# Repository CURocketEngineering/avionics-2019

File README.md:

## Deprecated
For more information, visit the [new, Python implementation](https://github.com/CURocketEngineering/avionics_main).

### About
Clemson University Rocket Engineering (CURE) Avionics subteam program files. 
Powers CURE's competitive and non-competitive rockets. Used in the 
Intercollegiate Rocket Engineering Competition. Begun by Foster McLane, 2016.

### Documentation
* [`base/`](base/)
  * Code ran on the CURE base station for communication and telemetry
  * `main.py` for basic communication
  * `mpl.py` for graphical interpretation
  * `mpl_simulator.py` for simulating graphical interpretation
* [`cad/`](/cad)
  * Files for electrically engineering components in `eagle`
* [`data/`](data/)
  * Flight data
  * `jsongrapher.py` for ensuring simulation (and actual) data 
  * ['Complete simulation'](data/sim_data_graphed) for pictures of complete simulations
* [`extra/`](extra/)
  * Testing
  * GPS and XBEE `.ino` files
* [`main/`](main/)
  * Code ran on CURE rockets used for data collection, state changes, and telemetry
* [`pics/`](pics/)
  * Pictures used in this github
* [`xbee/bypass/`](xbee/bypass/)
  * Communication

### License
This project is licensed used the GNU General Public License v3.0

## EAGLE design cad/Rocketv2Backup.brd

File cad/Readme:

Sparkfun Names of sensors (in eagle "add" component):
   1. Venus GPS ->                   GPS/ VENUS638FLPX-L
   2. Atmospheric Sensor Breakout -> Sensors/ BME280
   3. 9DoF Sensor Stick ->           Sensors/ LSM9DS1
   4. Antenna ->                     RF/ XBEE

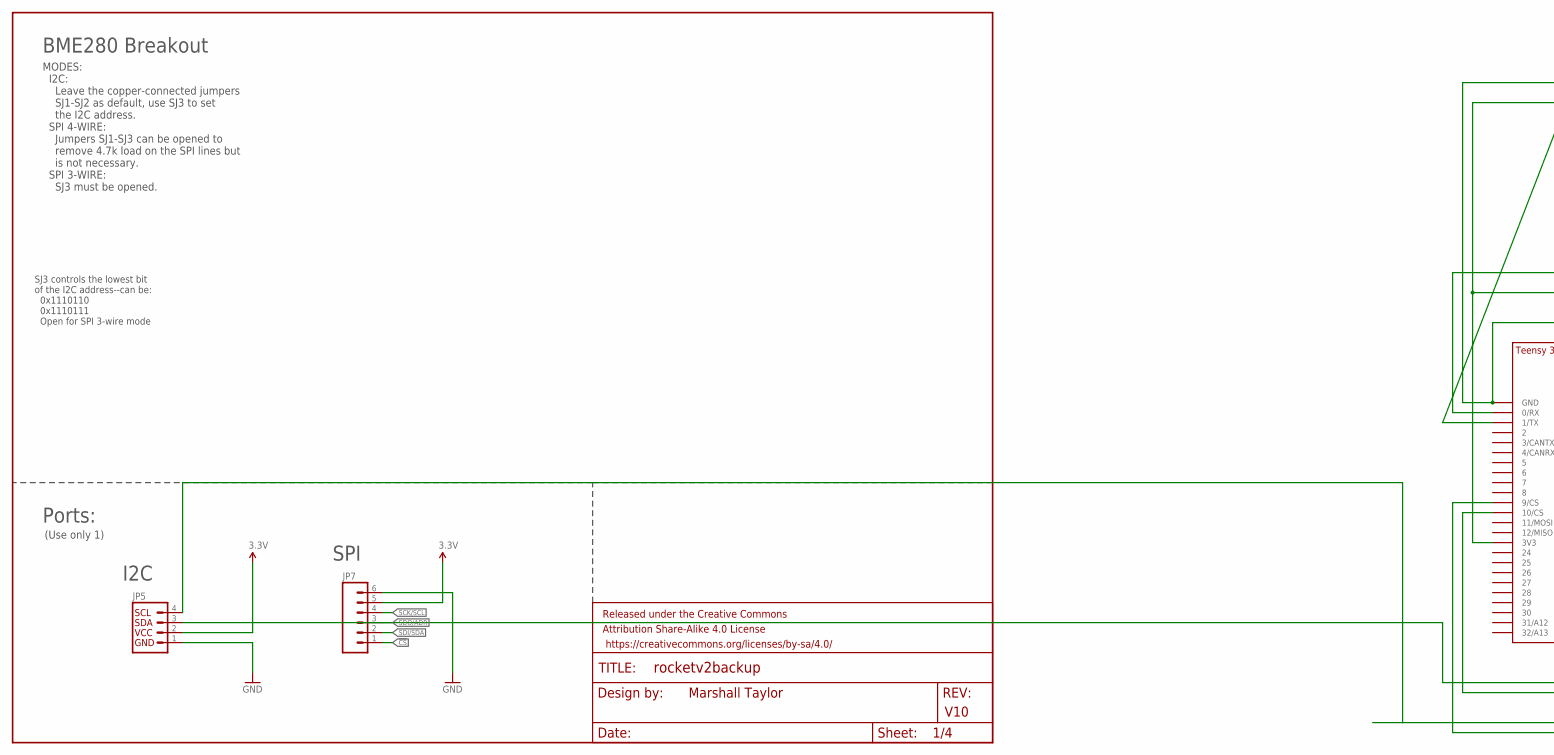
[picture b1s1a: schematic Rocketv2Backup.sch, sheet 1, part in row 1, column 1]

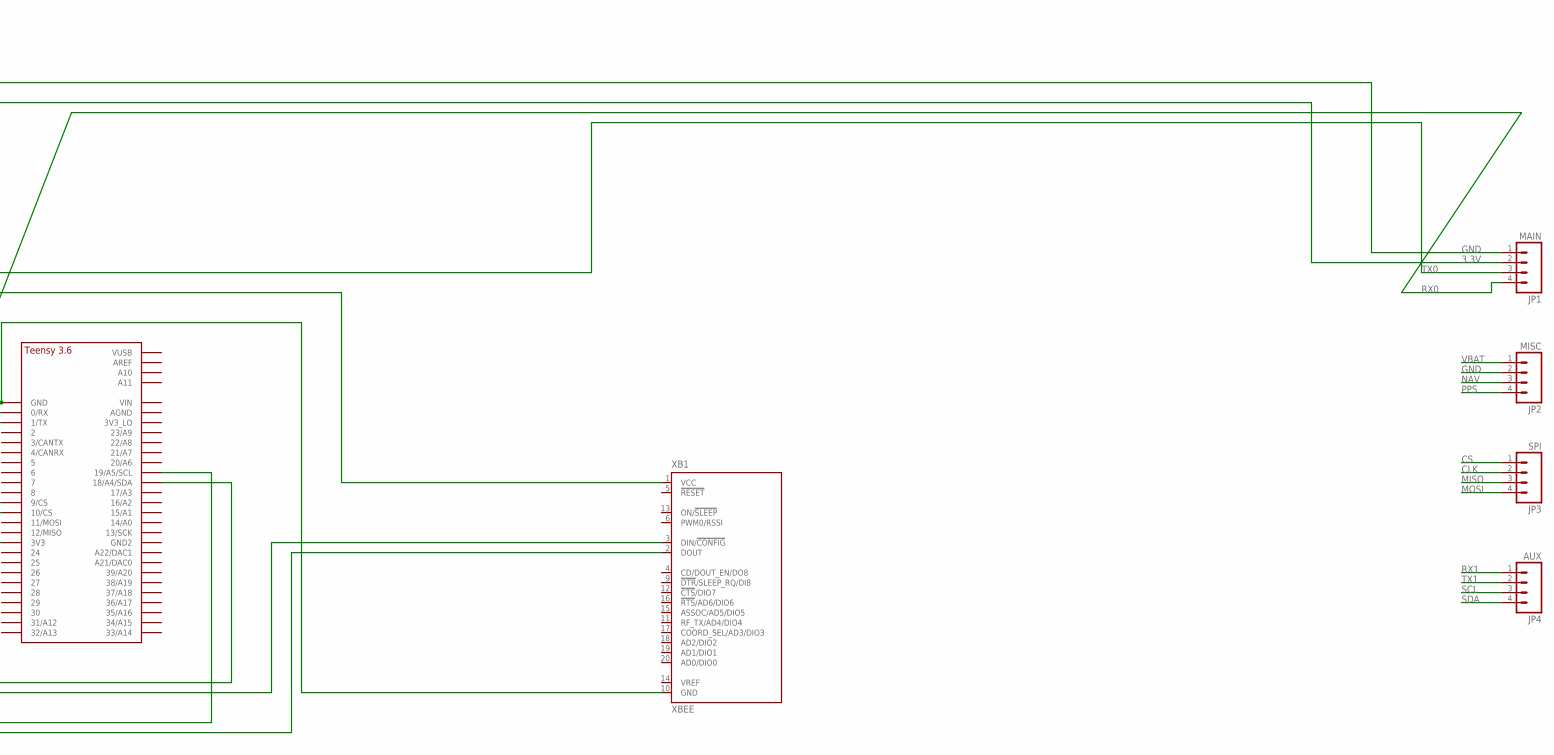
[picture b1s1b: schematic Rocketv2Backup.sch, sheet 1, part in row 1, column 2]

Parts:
FRAME3: FRAME-LETTER; CREATIVE_COMMONS
JP1: MAIN; 1X04
JP2: MISC; 1X04
JP3: SPI; 1X04
JP4: AUX; 1X04
JP5: I2C_STANDARD_NO_SILK; 1X04_NO_SILK
JP7: M06NO_SILK_FEMALE_PTH; 1X06_NO_SILK
U$1: TEENSY_3.5/3.6_BASIC
XB1: XBEE

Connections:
3.3V: JP1.2, JP5.2, JP7.5, U$1.3V3, XB1.1 (VCC)
!CS: JP7.1
CLK: JP3.2
CS: JP3.1
GND: JP1.1, JP2.2, JP5.1, JP7.6, U$1.GND, XB1.10 (GND); also elsewhere on the board
MISO: JP3.3
MOSI: JP3.4
unnamed: JP5.4, U$1.19/A5/SCL
unnamed: U$1.10/CS, XB1.3 (DIN/!CONFIG)
unnamed: U$1.9/CS, XB1.2 (DOUT)
NAV: JP2.3
PPS: JP2.4
RX0: JP1.4, U$1.1/TX
RX1: JP4.1
SCK/SCL: JP7.4
SCL: JP4.3; also elsewhere on the board
SDA: JP4.4; also elsewhere on the board
SDI/SDA: JP5.3, JP7.2, U$1.18/A4/SDA
SDO/ADR: JP7.3
TX0: JP1.3, U$1.0/RX
TX1: JP4.2
VBAT: JP2.1

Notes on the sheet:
Marshall Taylor
V10
BME280 Breakout
SJ3 controls the lowest bit of the I2C address--can be: 0x1110110 0x1110111 Open for SPI 3-wire mode
Ports:
(Use only 1)
I2C
SPI
MODES: I2C: Leave the copper-connected jumpers SJ1-SJ2 as default, use SJ3 to set the I2C address. SPI 4-WIRE: Jumpers SJ1-SJ3 can be opened to remove 4.7k load on the SPI lines but is not necessary. SPI 3-WIRE: SJ3 must be opened.

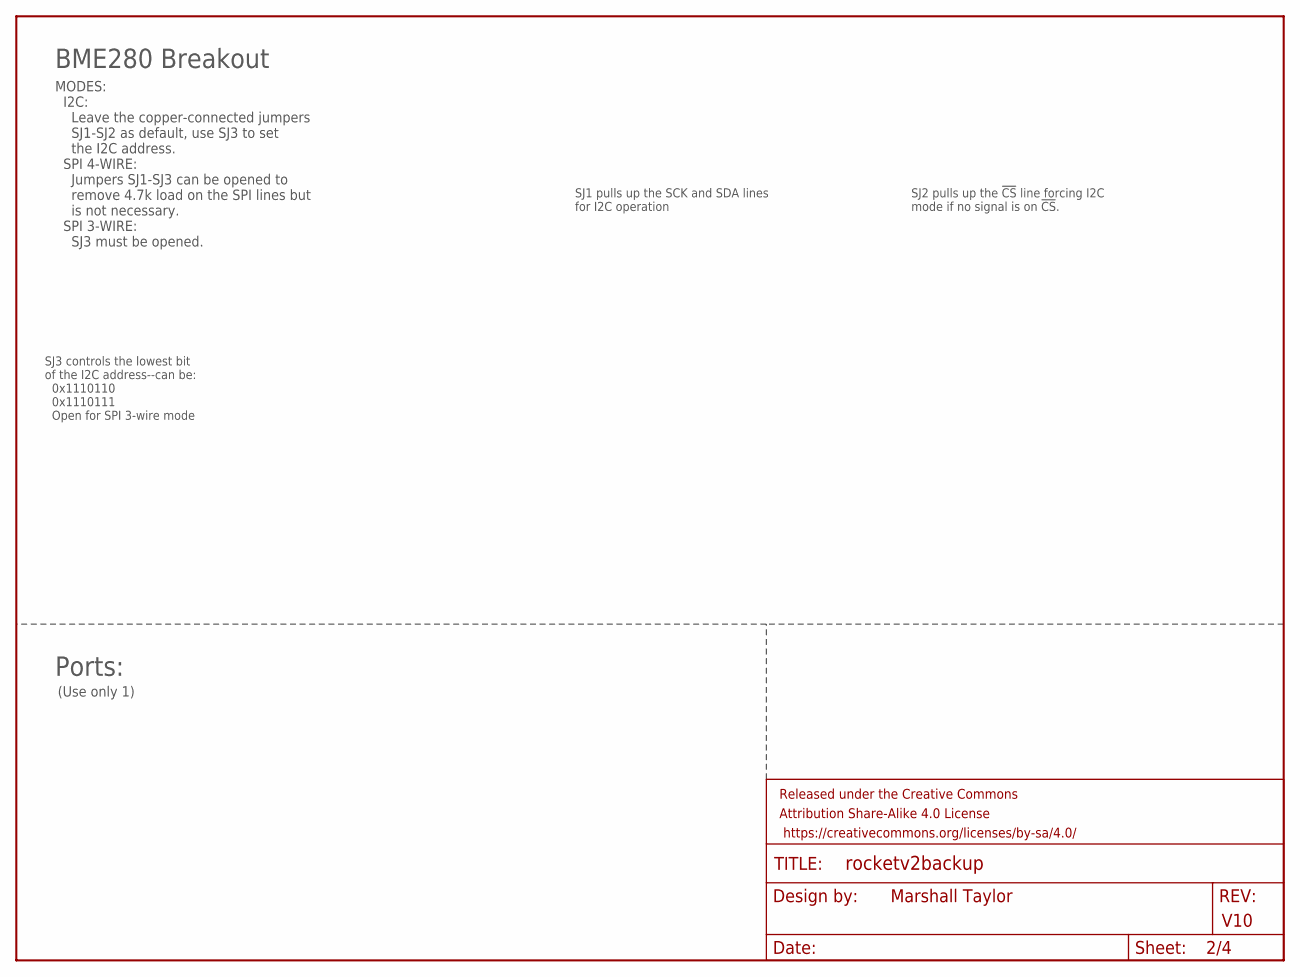
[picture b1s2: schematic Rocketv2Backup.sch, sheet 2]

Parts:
FRAME1: FRAME-LETTER; CREATIVE_COMMONS

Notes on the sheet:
Marshall Taylor
V10
BME280 Breakout
SJ3 controls the lowest bit of the I2C address--can be: 0x1110110 0x1110111 Open for SPI 3-wire mode
SJ1 pulls up the SCK and SDA lines for I2C operation
Ports:
(Use only 1)
MODES: I2C: Leave the copper-connected jumpers SJ1-SJ2 as default, use SJ3 to set the I2C address. SPI 4-WIRE: Jumpers SJ1-SJ3 can be opened to remove 4.7k load on the SPI lines but is not necessary. SPI 3-WIRE: SJ3 must be opened.
SJ2 pulls up the !CS! line forcing I2C mode if no signal is on !CS!.

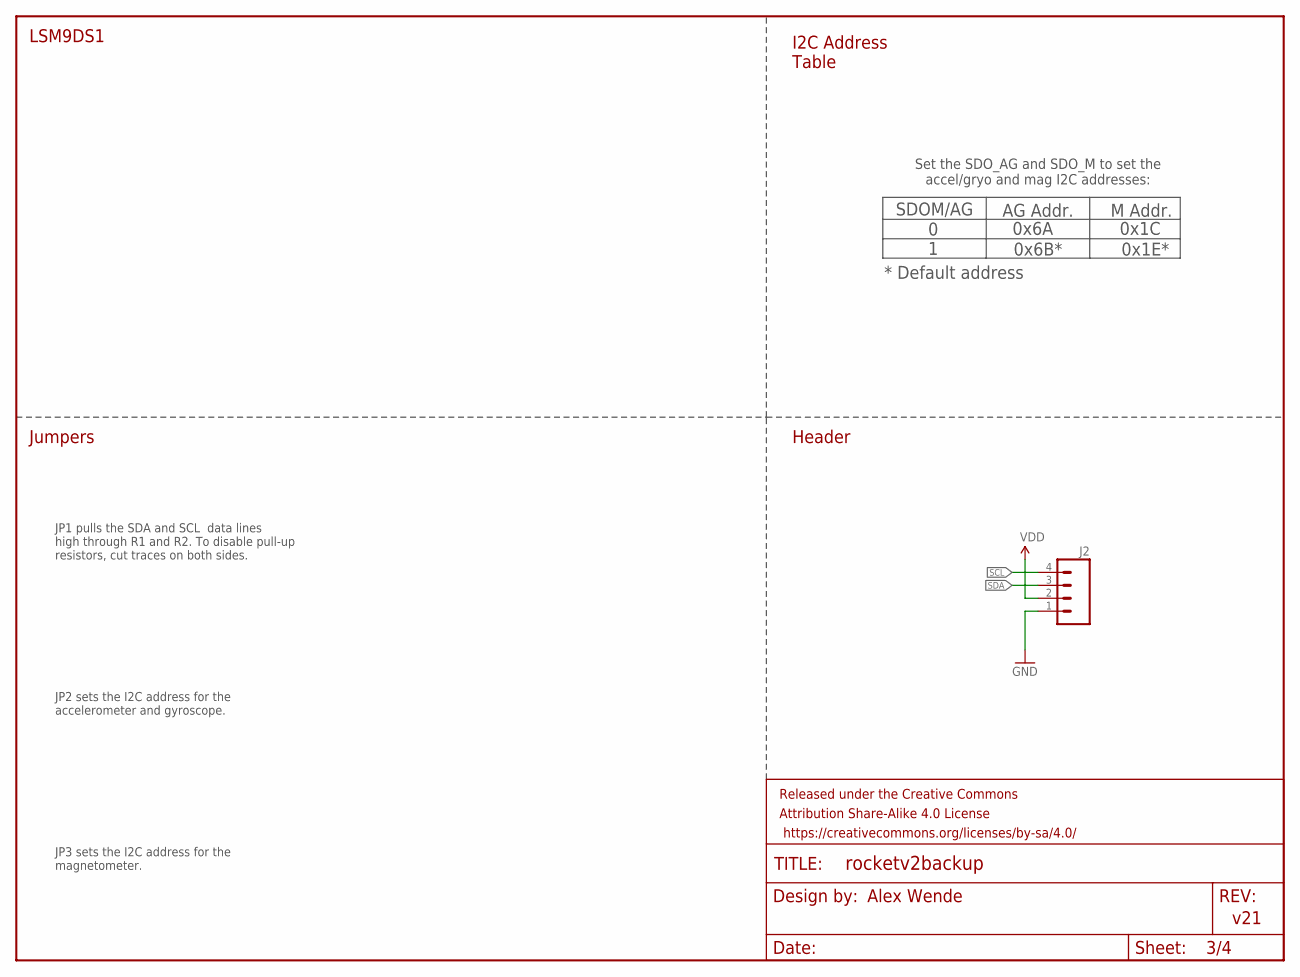
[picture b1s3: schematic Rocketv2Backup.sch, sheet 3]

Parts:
FRAME2: FRAME-LETTER; CREATIVE_COMMONS
J2: M04NO_SILK_ALL_ROUND; 1X04_NO_SILK_ALL_ROUND

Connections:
GND: J2.1; also elsewhere on the board
SCL: J2.4; also elsewhere on the board
SDA: J2.3; also elsewhere on the board
VDD: J2.2

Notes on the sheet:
Alex Wende
v21
LSM9DS1
SDOM/AG
AG Addr.
0 1
M Addr.
Set the SDO_AG and SDO_M to set the accel/gryo and mag I2C addresses:
I2C Address Table
Header
Jumpers
JP1 pulls the SDA and SCL data lines high through R1 and R2. To disable pull-up resistors, cut traces on both sides.
JP2 sets the I2C address for the accelerometer and gyroscope.
JP3 sets the I2C address for the magnetometer.
0x6A
0x6B*
0x1C
0x1E*
* Default address

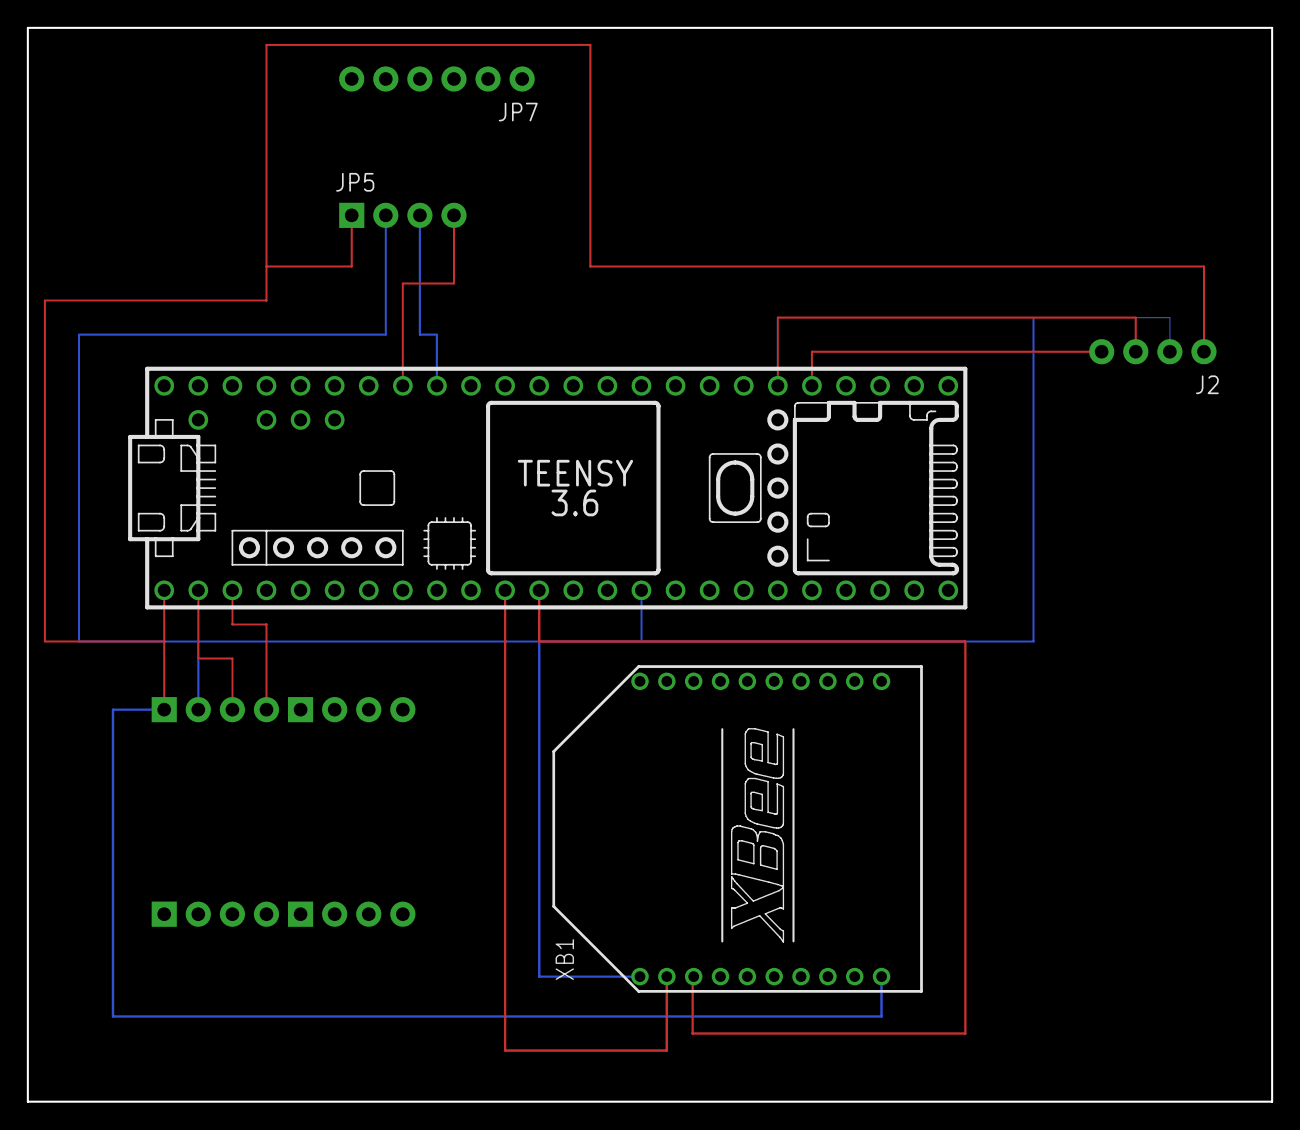
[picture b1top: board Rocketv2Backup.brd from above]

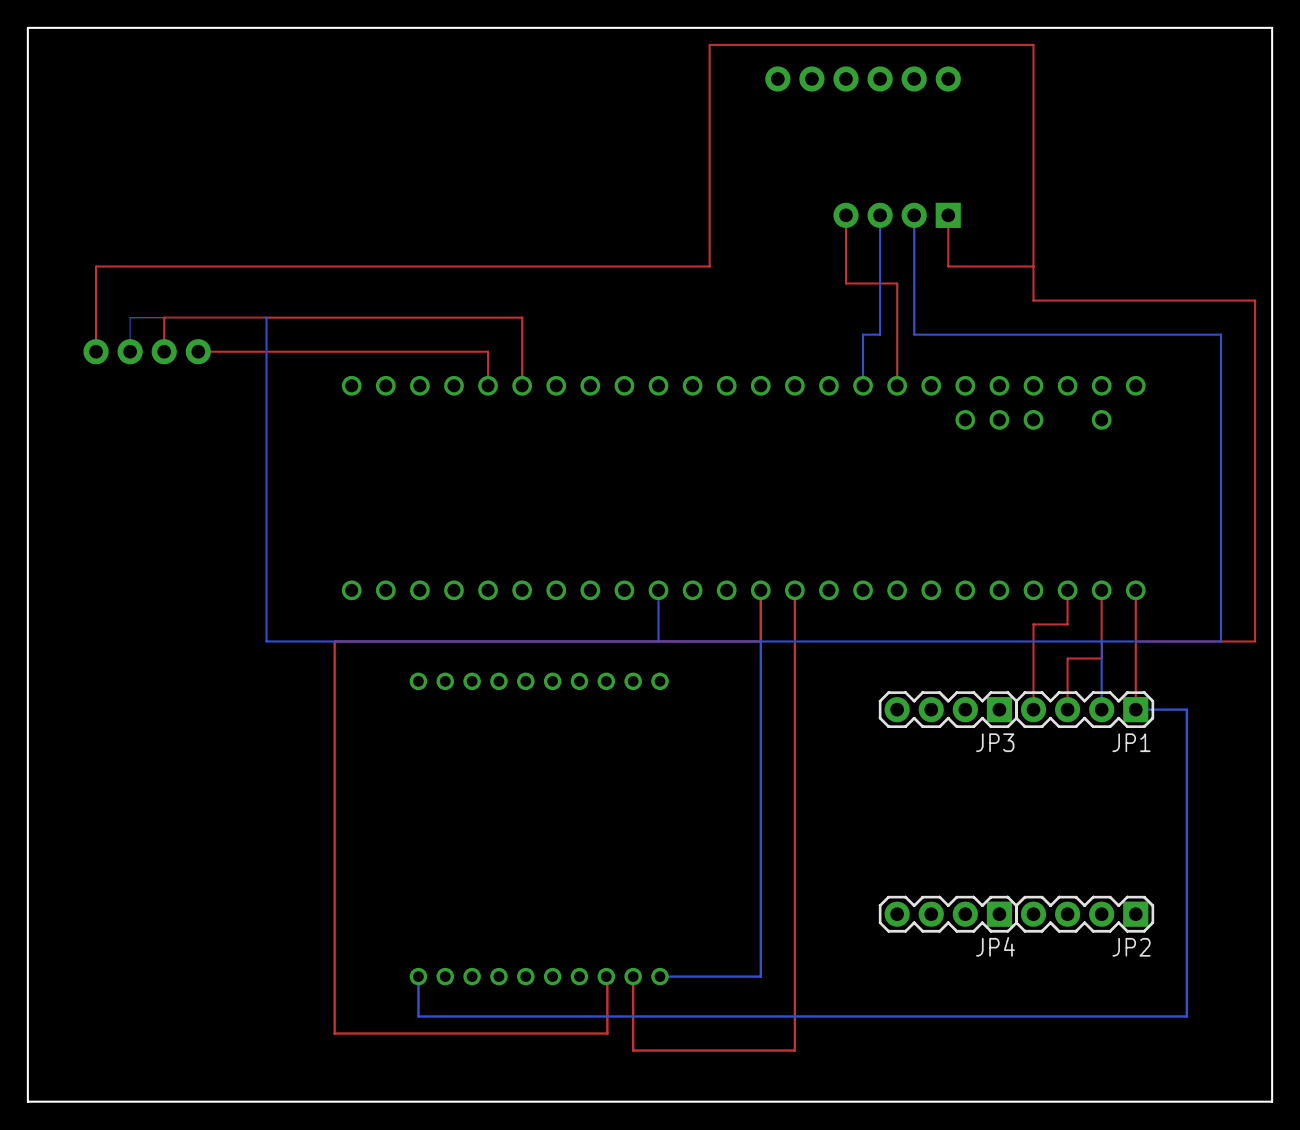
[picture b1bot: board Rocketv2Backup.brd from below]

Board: 2 copper layers, 92.7 x 80.0 mm, 12 parts (4 on the bottom side), 10 nets.

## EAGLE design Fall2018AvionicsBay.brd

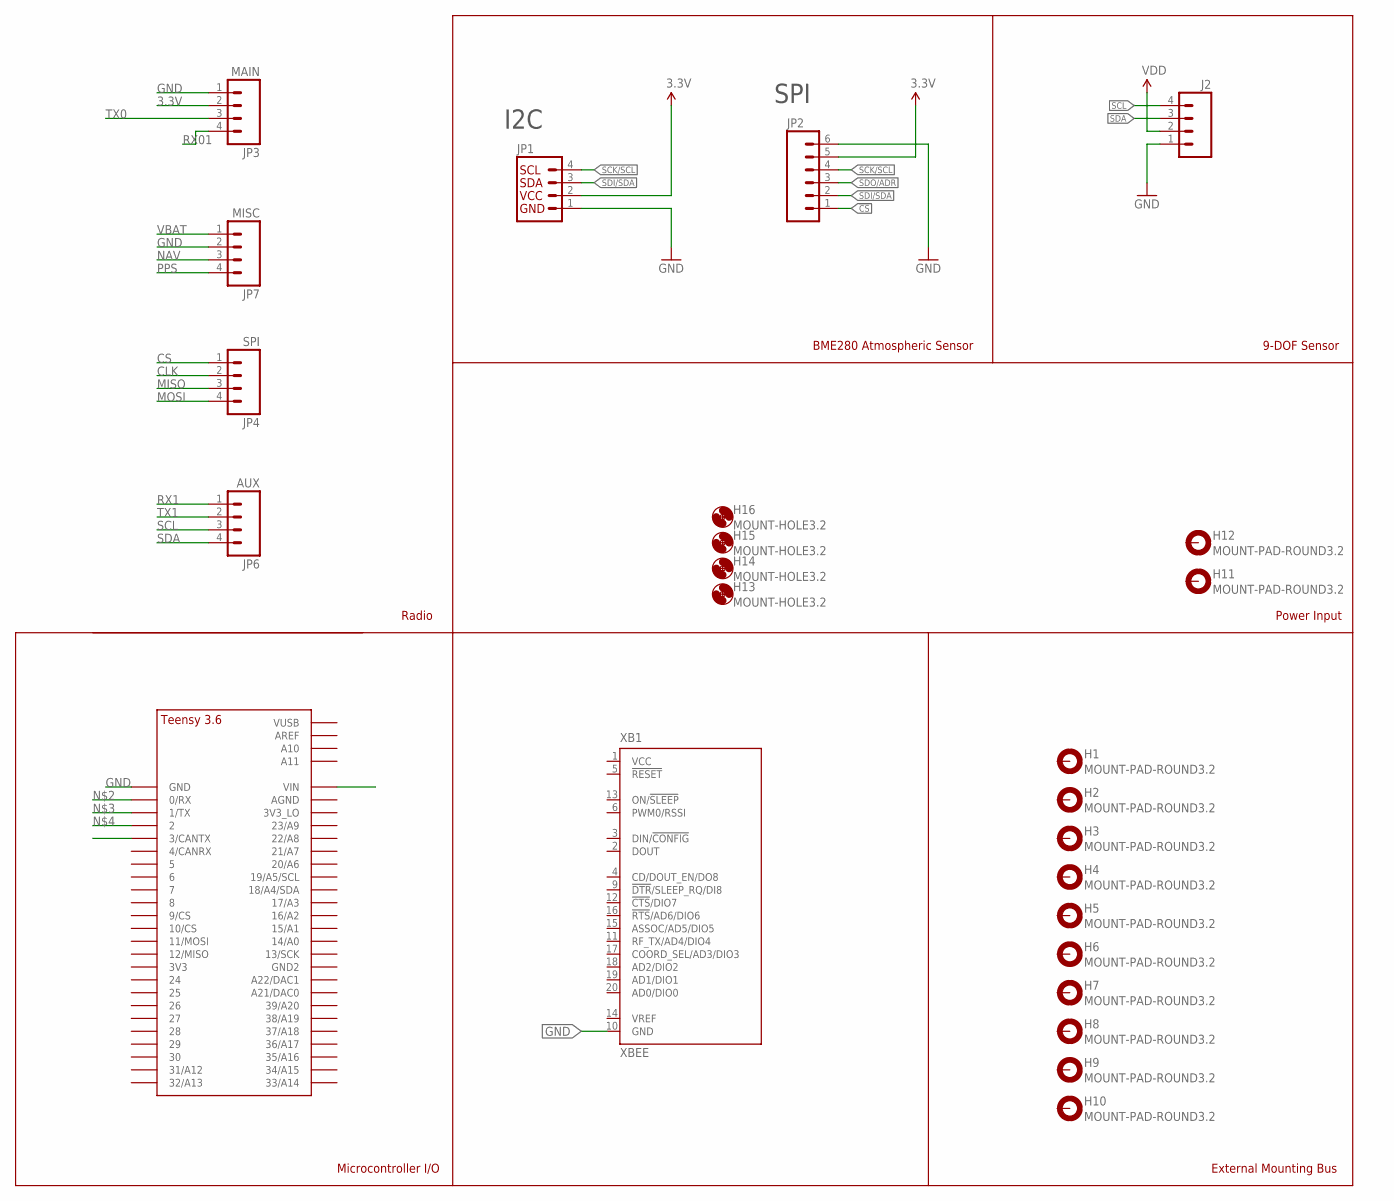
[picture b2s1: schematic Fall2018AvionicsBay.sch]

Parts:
H1, H2, H3, H4, H5, H6, H7, H8, H9, H10, H11, H12: MOUNT-PAD-ROUND3.2; 3,2-PAD
H13, H14, H15, H16: MOUNT-HOLE3.2; 3,2
J2: M04NO_SILK_ALL_ROUND; 1X04_NO_SILK_ALL_ROUND
JP1: I2C_STANDARD_NO_SILK; 1X04_NO_SILK
JP2: M06NO_SILK_FEMALE_PTH; 1X06_NO_SILK
JP3: MAIN; 1X04
JP4: SPI; 1X04
JP6: AUX; 1X04
JP7: MISC; 1X04
U$1: TEENSY_3.5/3.6_BASIC
XB1: XBEE

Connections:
3.3V: JP1.2, JP2.5, JP3.2
!CS: JP2.1
CLK: JP4.2
CS: JP4.1
GND: J2.1, JP1.1, JP2.6, JP3.1, JP7.2, U$1.GND, XB1.10 (GND)
MISO: JP4.3
MOSI: JP4.4
NAV: JP7.3
PPS: JP7.4
RX1: JP6.1
RX01: JP3.4
SCK/SCL: JP1.4, JP2.4
SCL: J2.4, JP6.3
SDA: J2.3, JP6.4
SDI/SDA: JP1.3, JP2.2
SDO/ADR: JP2.3
TX0: JP3.3
TX1: JP6.2
VBAT: JP7.1
VCC: XB1.1 (VCC)
VDD: J2.2

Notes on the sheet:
Microcontroller I/O
Radio
9-DOF Sensor
I2C
SPI
BME280 Atmospheric Sensor
External Mounting Bus
Power Input

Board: 2 copper layers, 25 parts (4 on the bottom side), 6 nets, no tracks yet.

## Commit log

2017-03-02 add basic kicad project
2017-03-02 add wip schematic
2017-03-06 add more wip main schematic
2017-03-08 add completed panel schematic revision 1
2017-03-08 add mostly complete main section
2017-03-08 finalize main section
2017-03-28 add preliminary boards
2017-04-18 update main board with more compact footprint
2017-04-18 adjust regulator pad
2017-04-25 add board outlines
2017-04-25 remove payload project
2017-05-09 patch in arming LED and fix backwards power caps
2017-05-09 fill zone for main board
2017-05-09 fix wiring of latch
2017-05-09 add pull-up resistor to reset pin
2017-05-09 move cad files to cad folder and add skeleton source code
2017-05-10 force initial button state and fix crystal pins
2017-05-10 reconnect accelerometer to adc pins
2017-05-10 add relevant data files directory
2017-05-10 swap ready and reset buttons
2017-05-11 add more misc board fixes
2017-05-15 add sample flight data file
2017-05-15 add XBee example programs
2017-05-16 moving main board information out of the way
2017-05-16 adjust which values are silkscreened
2017-05-16 add heading comments
2017-05-16 add mounting holes
2017-05-16 fix accelerometer connection
2017-05-16 add code to measure accelerometer and barometer data
2017-05-16 add mapping values
2017-05-19 add transmission attempts to latency
2017-05-19 add state machine to main program
2017-05-19 separate main and payload programs
2017-05-20 add flight logic
2017-05-28 fix syntax and turn off terminal connections on halt
2017-06-01 break up fall phase and make all LEDs being green meaning successful recovery
2017-06-09 add absolute altitude calculation
2017-06-09 increase precision of altitude calculation
2017-06-09 fix unconnected GND net in panel
2017-06-09 add pressure to flight data
2017-06-09 add debug mode which reads sensors from serial
2017-06-09 add test program which simulates sensor values and payload
2017-06-09 fill out pin numbers and allow programming with usbtiny
2017-06-10 change LEDs to command anode and release rev 3
2017-06-10 add support for continuing flight even if main computer resets
2017-06-10 add automatic board detection based on directory
2017-06-10 fix port numbers and save debug LEDs in EEPROM
2017-06-11 add diode after flop and start hand-made traces
2017-06-11 change board back to uno until we have 8MHz crystal/resonator
2017-06-11 fix LED output and store ground in EEPROM
2017-06-12 change payload addr to 8
2017-06-12 fix backwards MOSFETs
2017-06-16 adjust pinout to revision 2.718281828459045
2017-06-16 update programming for circuit board
2017-06-16 make main program give a little more startup information
2017-06-16 make test program use PROGMEM
2017-06-20 move to revision 4 of boards
2017-06-20 add LED test
2017-06-20 add more serial debug to test
2017-06-20 update altimeter setting for Truth or Consequences
2017-06-20 fix edge cuts on panel
2017-06-20 add startup delay for main computer when debugging
2017-06-20 rename debug to radio header
2017-06-21 attempt to use utf8 in serial monitor
2017-06-21 add basic payload program structure
2017-06-21 rename XBeeProgram to XBeePass
2017-06-21 rename payload time to timing to avoid name clash
2017-06-22 switch payload communication to UART instead of I²C
2017-06-22 update kicad project files
2017-06-22 add payload sensor data and communication
2017-06-22 remove remaining references to Wire
2017-06-22 make dp a signed integer
2017-06-22 rearrange payload<->computer interaction and update barometer reading code
2017-06-22 adjust test flight data for new units
2017-06-22 update payload comm for new units
2017-06-22 update altimeter reading
2017-06-22 setup finished communication between main<->payload<->base
2017-06-22 change to python2
2017-06-22 fix uarts and disable missing sensors
2017-06-22 add more python to gitignore
2017-06-22 disable sound as well
2017-06-22 remove unused init calls
2017-06-22 fix sound init
2017-06-22 fix init assignment in sound
2017-06-22 fix box arguments
2017-06-22 fix misnamed label
2017-06-22 fix another variable
2017-06-22 more fixes
2017-06-22 disable magnetometer too
2017-06-22 more unfound fixes
2017-06-22 disable more stuff
2017-06-22 fix state reference
2017-06-22 have more code
2017-06-22 more code...
2017-06-22 print data transfered
2017-06-22 add more python2 compatibility
2017-06-22 make gps fail on unexpected input
2017-06-22 add GPS size safeguard
2017-06-22 add working GPS
2017-06-22 fix radio uart
2017-06-22 do radio over USB OTG
2017-06-23 add payload arduino GPS code
2017-06-23 add working GPS program
2017-06-23 make payload get GPS over I²C
2017-06-23 use i2c correctly in gps
2017-06-23 fix error in test program
2017-06-23 add encoding to python program
2017-06-23 use floats for macro defines
2017-06-23 add state names and remote disarm
2017-06-23 adjust max ignite time
2017-06-24 add blackbox in base station as well
2017-06-24 make small misc payload fixes
2017-06-25 reenable payload stuff
2017-06-25 separate main and extra programs
2017-10-08 update base program for main computer with GPS
2017-10-08 move XBeePass to prog
2017-10-08 read GPS and contact base station
2017-10-09 fix blackbox import
2017-10-12 remove dependence of payload on main computer
2017-10-12 Remove wire protocol in GPS program
2017-10-13 make SoftwareSerial optional in XBeeEcho
2017-10-13 use tested readGps function
2017-10-13 fix whitespace
2017-10-13 change board definition for Main
2017-10-13 add working copies
2017-10-13 make idle rerun each tick
2017-10-13 rate limit idle
2017-10-13 make comm more resilient
2017-10-13 ignore blackbox files
2017-10-13 fix gps comm
2017-11-08 remove debug stuff
2017-11-08 fix small pointless kicad issue
2017-11-15 remove cad files
2017-11-15 remove atmega328w.png
2017-11-29 Split main_v0.2
    Split apart the initial main v0.2 file into main.ino and various .h/.cpp files. Compiles correctly on (Windows) Arduino IDE and PlatformIO (Atom package).
2017-12-03 add wip refactoring for function names
2018-01-11 move global to pins and separate debug
2018-01-16 add json.h
2018-01-23 Initial 9DoF sensor calculations
    This is not integrated at all with the rest of the /main files. This is a preliminary idea as to how the 9DoF sensor may be implemented in the future. Deviation calculations use the gyroscope's X and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
    Uses Arduino's Serial.print to display data in the Serial Monitor (usually located in the Arduino IDE; not sure if Linux is able to view this).
    The programs should theoretically work, but no testing has been done.
    Requires the SparkFunLSM9DS1.h library (located https://github.com/sparkfun/SparkFun_LSM9DS1_Arduino_Library).
2018-01-29 An attempt to incorporate the new barometer.
2018-01-31 Added in JSON
    Hopefully everything works, this is the first time I worked with JSON in any form.
2018-02-07 Fixed some barometer things
2018-02-07 9DoF and other edits
2018-02-15 update automatically finding the Arduino dir in macOS
2018-02-15 move libraries
2018-02-15 Create Schematics and Data Sheets
2018-02-20 add sparkfun lsm9ds1 library
2018-02-20 move libraries to main folder
2018-02-21 bring barometer up to speed
2018-02-21 move functions out of gps
2018-02-22 update communication for json
2018-02-22 dos2unix all of the files and add datalogging
2018-03-06 add GPS date/time and add compilation fixes
2018-03-06 rename Datasheets and Schematics to cad
2018-03-06 finish new communication
2018-03-06 clean up cad a little
2018-03-08 2018-03-07 changes
2018-03-08 Removed struct, added json.
2018-03-08 quickfix
2018-03-14 clean up style (i.e. remote end-of-line whitespace)
2018-03-14 change to new comm standard
2018-03-14 fix little issues in communication.cpp
2018-03-15 update cad for combined i2c
2018-03-15 make gps use serial2
2018-03-15 remove compiler warnings
2018-03-15 ignore backup cad files
2018-03-16 add LSM/BME test code
2018-03-16 fix python syntax error
2018-03-18 print a newline to serial after message
2018-03-24 fix barometer reading
2018-03-24 add attitude to sensor output
2018-03-24 fix issue with same data across 9dof sensor
2018-03-24 move pins to pins.h
2018-03-28 urwid base
2018-03-28 Initial creation of init and update functions
2018-03-28 Fixed some issues as per Harrison
2018-03-28 fixes
2018-03-28 trying threading lol
2018-03-28 added fake data and created accompanying function
2018-03-28 add control switch
2018-03-29 adjust base station for new json
2018-04-04 urwid update
2018-04-04 Updated urw.py
2018-04-04 add emulator for csv data
2018-04-04 Updates single graph completely
2018-04-04 quickupdate
2018-04-04 commented
2018-04-04 replace fix
2018-04-05 continually send none command
2018-04-05 make halt go to idle instead of sleeping the processor
2018-04-06 plotting code
2018-04-06 add parse to mpl.py
2018-04-06 hotfix
2018-04-09 Some experimentation with mpl
2018-04-11 Test fixes.
2018-04-11 Removed comm.init(), must wait to show fake data if error.
2018-04-12 add simulation
2018-04-18 add sim data
2018-04-18 ifdef flight.h
2018-04-19 color fix for comm graphs
2018-05-21 remove unused payload code
2018-05-21 Added Board and Schematic files
2018-05-30 Added speed function and makeshift speedometer
2018-06-05 miscellaneous changes
2018-06-06 allow XBeePass to use SoftwareSerial
2018-06-13 Begun work on simulation for fake data
2018-06-13 add SS for XBeeLatency
2018-06-13 move cad files
2018-06-14 fix main program
2018-06-18 graphed sim data
2018-06-18 adjust XBee communication
2018-06-18 remove pin collision
2018-06-18 move XBeePass
2018-06-19 fix datalog
2018-06-19 add XBeeBypass
2018-06-19 add possible delay before ejecting parachute
2018-06-20 make a few IREC changes
2018-06-21 more irec changes
2018-06-23 create teensy makefile
2018-06-23 move stuff to config.h
2018-06-23 add bypass src.uart
2018-06-23 remove bypass src.uart
2018-06-23 add speeds selector to makefile
2018-06-28 Updated graphing program
2018-07-07 make extra/makefile a link to main/makefile
2018-07-07 remove unnecessary sections from makefile
2018-07-07 make more irec changes
2018-07-07 automatically reboot on upload
2018-07-07 update makefile
2018-07-08 fix running make boards or make clean without setting speed
2018-09-21 license code under GPLv3
    enacted by all developers of the current program 2018-09-21
2018-09-24 adding readmes
2018-10-07 those qs
2018-10-07 read
2018-10-07 foster questions
2018-10-07 foster qs
2018-10-07 updated readme and moved eagle files
2018-10-07 moved files
2018-10-09 updated READMEs
2018-10-10 documentation and begin fixing mpl.py
2018-10-29 Visual with quickbox
2018-10-29 Updating for visual
2018-10-30 bug fix and visual example
2018-10-31 beta gui
2018-10-31 mpl documentation
2018-10-31 pre-meeting
2018-10-31 update ignore
2019-01-17 mpl.py major graphing update
2019-01-18 data area
2019-01-21 edited error msg
2019-04-24 bug fix update readmes
2019-05-17 Removed unecessary graphing
2019-05-28 updated for a new year
2019-05-29 fixed wire.h issue, and toggleRelay bug
2019-06-14 qwiic
2019-06-14 ejection test
2019-06-14 ready for ejection
2019-11-20 Made a note about deprecation in readme.

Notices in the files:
parts and their libraries:
SparkFun-Connectors: Licensing: Creative Commons ShareAlike 4.0 International - https://creativecommons.org/licenses/by-sa/4.0
SparkFun-Aesthetics: Released under the Creative Commons Attribution Share-Alike 4.0 License
SparkFun-Aesthetics: https://creativecommons.org/licenses/by-sa/4.0
